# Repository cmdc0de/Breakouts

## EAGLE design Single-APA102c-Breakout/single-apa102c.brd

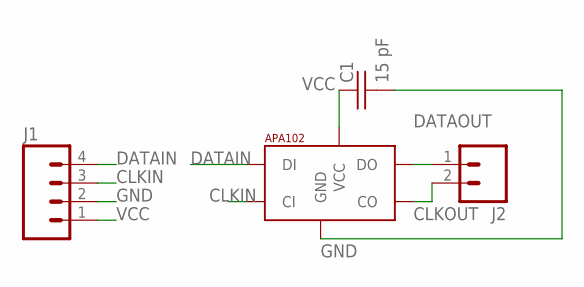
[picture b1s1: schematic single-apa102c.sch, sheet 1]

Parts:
C1: 15 pF; C0805K
J1: M04PTH; 1X04
J2: M02PTH; 1X02
U$1: APA1025050; APA102_5050

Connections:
CLKIN: J1.3, U$1.5 (CI)
CLKOUT: J2.2, U$1.2 (CO)
DATAIN: J1.4, U$1.4 (DI)
DATAOUT: J2.1, U$1.3 (DO)
GND: C1.2, J1.2, U$1.6 (GND)
VCC: C1.1, J1.1, U$1.1 (VCC)

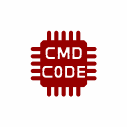
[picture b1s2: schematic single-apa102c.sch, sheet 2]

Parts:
U$2: CMD_C0DE_LOGOCMD_CODE_LOGO_TOP_COPPER; CMD_C0DE_LOGO_TOP_COPPER

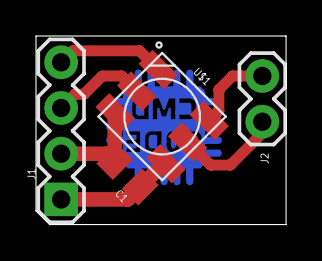
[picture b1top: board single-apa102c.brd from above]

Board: 2 copper layers, 13.9 x 10.5 mm, 5 parts (1 on the bottom side), 6 nets.

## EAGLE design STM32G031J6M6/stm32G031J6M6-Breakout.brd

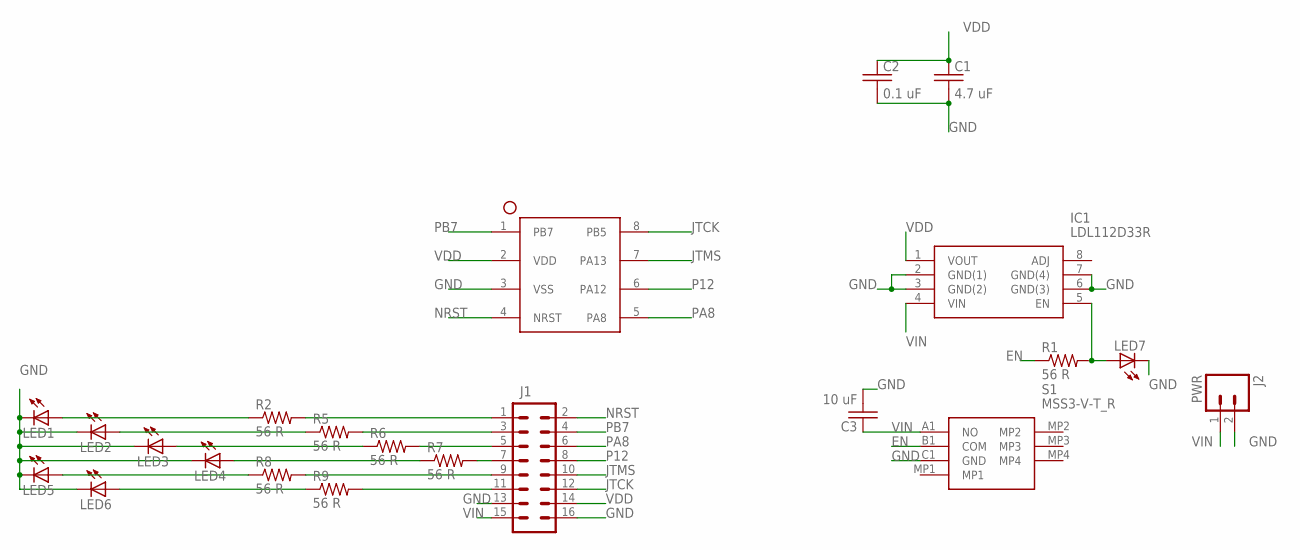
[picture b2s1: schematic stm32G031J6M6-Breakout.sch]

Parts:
C1: 4.7 uF; C0805K
C2: 0.1 uF; C0805K
C3: 10 uF; C0805K
IC1: LDL112D33R; SOIC127P600X175-8N
J1: M08X2; 2X8
J2: PWR; 1X02
LED1, LED2, LED3, LED4, LED5, LED6, LED7: LED1206; LED-1206
R1, R2, R5, R6, R7, R8, R9: 56 R; 1206
S1: MSS3-V-T_R; MSS3VTR
U$1: STM32G031S08N; SOIC127P600X175-8N

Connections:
EN: R1.1, S1.B1 (COM)
GND: C1.2, C2.2, C3.2, IC1.2 (GND(1)), IC1.3 (GND(2)), IC1.6 (GND(3)), IC1.7 (GND(4)), J1.13, J1.16, J2.2, LED1.C, LED2.C, LED3.C, LED4.C, LED5.C, LED6.C, LED7.C, S1.C1 (GND), U$1.3 (VSS)
JTCK: J1.12, U$1.8 (PB5)
JTMS: J1.10, U$1.7 (PA13)
unnamed: J1.1, R2.2
unnamed: J1.3, R5.2
unnamed: J1.5, R6.2
unnamed: J1.7, R7.2
unnamed: J1.9, R8.2
unnamed: J1.11, R9.2
unnamed: LED1.A, R2.1
unnamed: LED2.A, R5.1
unnamed: LED3.A, R6.1
unnamed: LED4.A, R7.1
unnamed: LED5.A, R8.1
unnamed: LED6.A, R9.1
unnamed: IC1.5 (EN), LED7.A, R1.2
NRST: J1.2, U$1.4 (NRST)
P12: J1.8, U$1.6 (PA12)
PA8: J1.6, U$1.5 (PA8)
PB7: J1.4, U$1.1 (PB7)
VDD: C1.1, C2.1, IC1.1 (VOUT), J1.14, U$1.2 (VDD)
VIN: C3.1, IC1.4 (VIN), J1.15, J2.1, S1.A1 (NO)

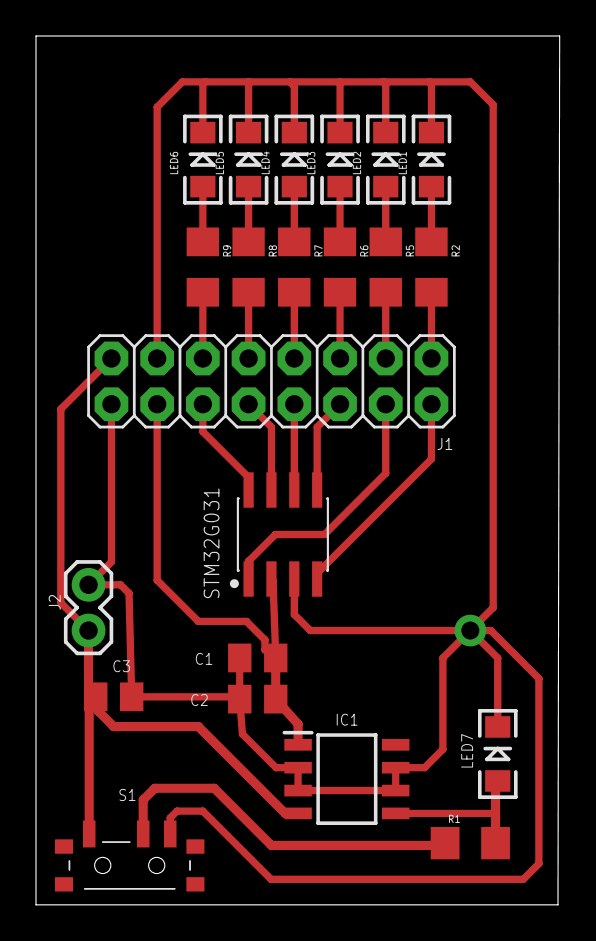
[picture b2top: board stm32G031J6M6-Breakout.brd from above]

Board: 2 copper layers, 29.1 x 48.3 mm, 22 parts (0 on the bottom side), 23 nets.

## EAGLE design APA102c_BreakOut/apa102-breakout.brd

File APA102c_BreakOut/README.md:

# APA102c_BreakOut
Holds eagle design and files for an apa102 50x50 breakout board

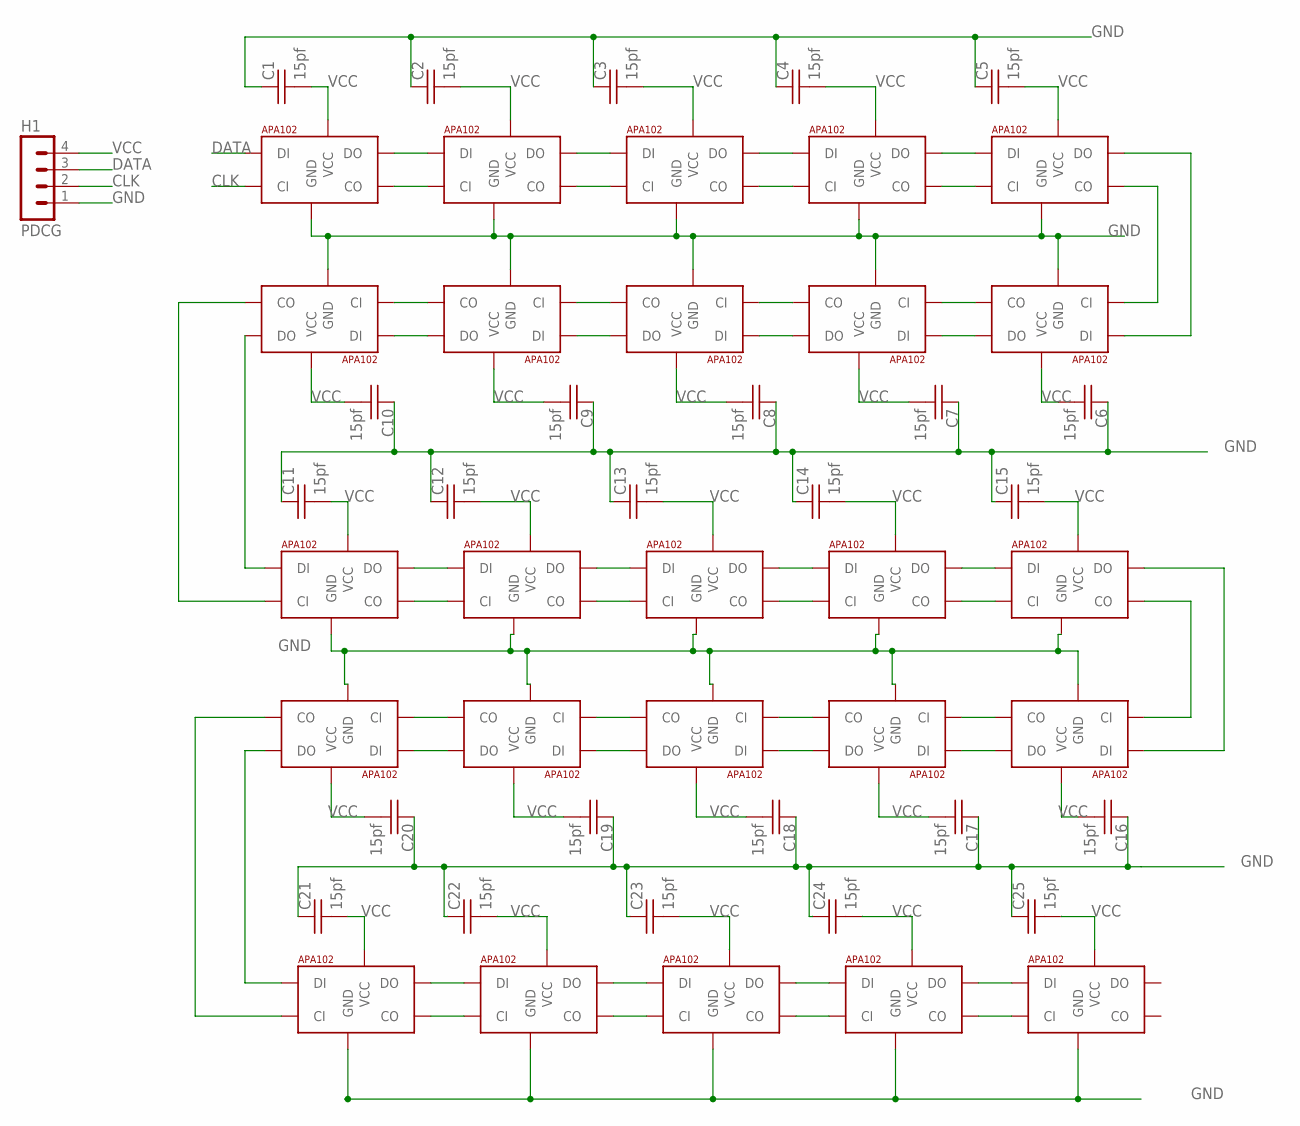
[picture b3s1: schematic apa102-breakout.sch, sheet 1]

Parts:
C1, C2, C3, C4, C5, C6, C7, C8, C9, C10, C11, C12, C13, C14, C15, C16, C17, C18, C19, C20, C21, C22, C23, C24, C25: 15pf; C0805
H1: PDCG; MA04-1
U$2, U$3, U$4, U$5, U$6, U$7, U$8, U$9, U$10, U$11, U$12, U$13, U$14, U$15, U$16, U$17, U$18, U$19, U$20, U$21, U$22, U$23, U$24, U$25, U$26: APA1025050; APA102_5050

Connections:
CLK: H1.2, U$2.5 (CI)
DATA: H1.3, U$2.4 (DI)
GND: C1.1, C2.1, C3.1, C4.1, C5.1, C6.1, C7.1, C8.1, C9.1, C10.1, C11.1, C12.1, C13.1, C14.1, C15.1, C16.1, C17.1, C18.1, C19.1, C20.1, C21.1, C22.1, C23.1, C24.1, C25.1, H1.1, U$2.6 (GND), U$3.6 (GND), U$4.6 (GND), U$5.6 (GND), U$6.6 (GND), U$7.6 (GND), U$8.6 (GND), U$9.6 (GND), U$10.6 (GND), U$11.6 (GND), U$12.6 (GND), U$13.6 (GND), U$14.6 (GND), U$15.6 (GND), U$16.6 (GND), U$17.6 (GND), U$18.6 (GND), U$19.6 (GND), U$20.6 (GND), U$21.6 (GND), U$22.6 (GND), U$23.6 (GND), U$24.6 (GND), U$25.6 (GND), U$26.6 (GND)
unnamed: U$2.3 (DO), U$3.4 (DI)
unnamed: U$2.2 (CO), U$3.5 (CI)
unnamed: U$3.3 (DO), U$4.4 (DI)
unnamed: U$3.2 (CO), U$4.5 (CI)
unnamed: U$4.3 (DO), U$5.4 (DI)
unnamed: U$4.2 (CO), U$5.5 (CI)
unnamed: U$5.3 (DO), U$6.4 (DI)
unnamed: U$5.2 (CO), U$6.5 (CI)
unnamed: U$6.3 (DO), U$7.4 (DI)
unnamed: U$6.2 (CO), U$7.5 (CI)
unnamed: U$7.3 (DO), U$8.4 (DI)
unnamed: U$7.2 (CO), U$8.5 (CI)
unnamed: U$8.2 (CO), U$9.5 (CI)
unnamed: U$8.3 (DO), U$9.4 (DI)
unnamed: U$9.2 (CO), U$10.5 (CI)
unnamed: U$9.3 (DO), U$10.4 (DI)
unnamed: U$10.2 (CO), U$11.5 (CI)
unnamed: U$10.3 (DO), U$11.4 (DI)
unnamed: U$11.2 (CO), U$12.5 (CI)
unnamed: U$11.3 (DO), U$12.4 (DI)
unnamed: U$12.3 (DO), U$13.4 (DI)
unnamed: U$12.2 (CO), U$13.5 (CI)
unnamed: U$13.3 (DO), U$14.4 (DI)
unnamed: U$13.2 (CO), U$14.5 (CI)
unnamed: U$14.3 (DO), U$15.4 (DI)
unnamed: U$14.2 (CO), U$15.5 (CI)
unnamed: U$15.3 (DO), U$16.4 (DI)
unnamed: U$15.2 (CO), U$16.5 (CI)
unnamed: U$16.3 (DO), U$17.4 (DI)
unnamed: U$16.2 (CO), U$17.5 (CI)
unnamed: U$17.3 (DO), U$18.4 (DI)
unnamed: U$17.2 (CO), U$18.5 (CI)
unnamed: U$18.2 (CO), U$19.5 (CI)
unnamed: U$18.3 (DO), U$19.4 (DI)
unnamed: U$19.2 (CO), U$20.5 (CI)
unnamed: U$19.3 (DO), U$20.4 (DI)
unnamed: U$20.2 (CO), U$21.5 (CI)
unnamed: U$20.3 (DO), U$21.4 (DI)
unnamed: U$21.3 (DO), U$22.4 (DI)
unnamed: U$21.2 (CO), U$22.5 (CI)
unnamed: U$22.3 (DO), U$23.4 (DI)
unnamed: U$22.2 (CO), U$23.5 (CI)
unnamed: U$23.3 (DO), U$24.4 (DI)
unnamed: U$23.2 (CO), U$24.5 (CI)
unnamed: U$24.3 (DO), U$25.4 (DI)
unnamed: U$24.2 (CO), U$25.5 (CI)
unnamed: U$25.3 (DO), U$26.4 (DI)
unnamed: U$25.2 (CO), U$26.5 (CI)
VCC: C1.2, C2.2, C3.2, C4.2, C5.2, C6.2, C7.2, C8.2, C9.2, C10.2, C11.2, C12.2, C13.2, C14.2, C15.2, C16.2, C17.2, C18.2, C19.2, C20.2, C21.2, C22.2, C23.2, C24.2, C25.2, H1.4, U$2.1 (VCC), U$3.1 (VCC), U$4.1 (VCC), U$5.1 (VCC), U$6.1 (VCC), U$7.1 (VCC), U$8.1 (VCC), U$9.1 (VCC), U$10.1 (VCC), U$11.1 (VCC), U$12.1 (VCC), U$13.1 (VCC), U$14.1 (VCC), U$15.1 (VCC), U$16.1 (VCC), U$17.1 (VCC), U$18.1 (VCC), U$19.1 (VCC), U$20.1 (VCC), U$21.1 (VCC), U$22.1 (VCC), U$23.1 (VCC), U$24.1 (VCC), U$25.1 (VCC), U$26.1 (VCC)

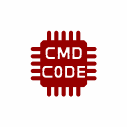
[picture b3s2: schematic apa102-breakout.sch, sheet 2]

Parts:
U$1: CMD_C0DE_LOGOCMD_C0DE_LOGO_TOP; CMD_C0DE_LOGO_TOP

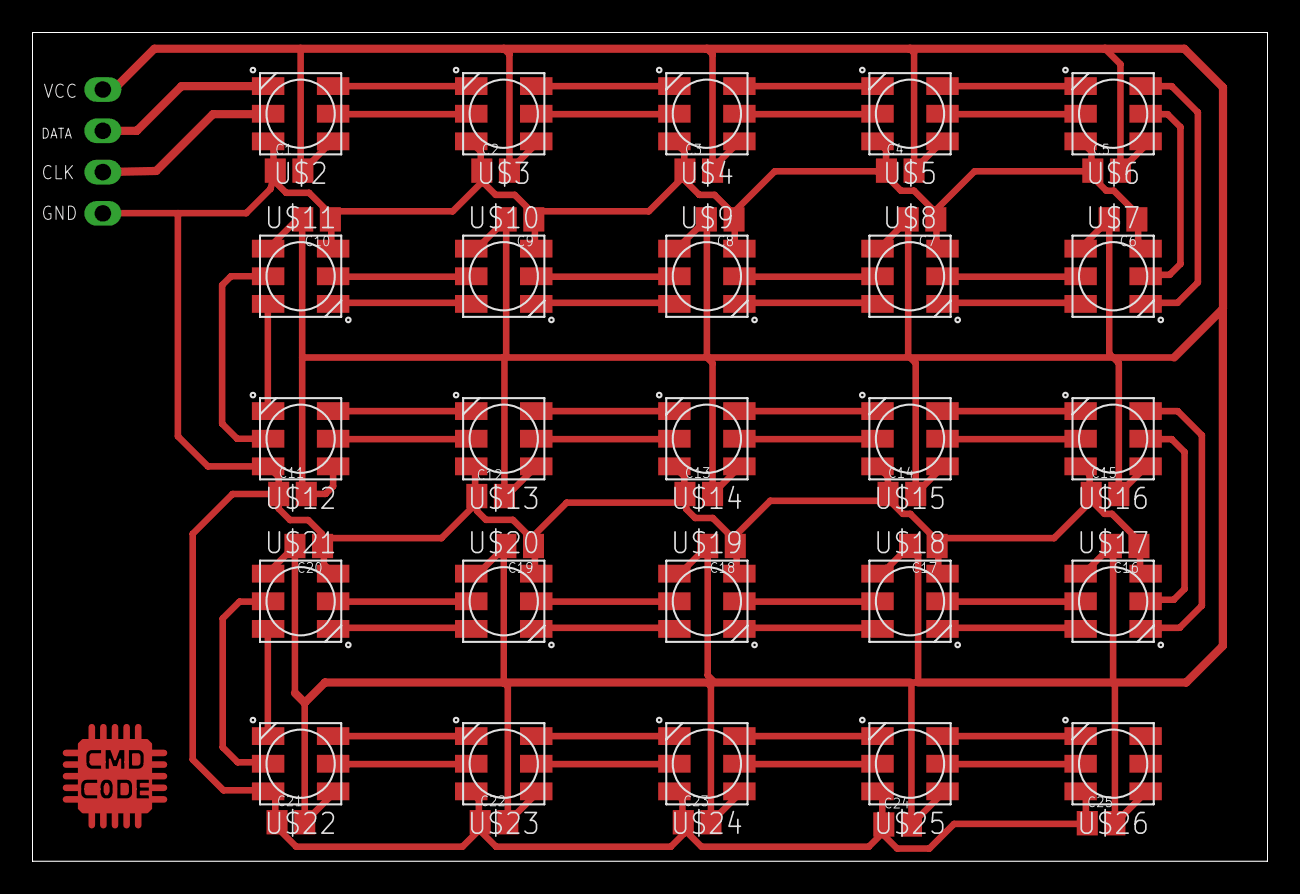
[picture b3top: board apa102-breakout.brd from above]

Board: 2 copper layers, 76.0 x 51.0 mm, 52 parts (1 on the bottom side), 52 nets.

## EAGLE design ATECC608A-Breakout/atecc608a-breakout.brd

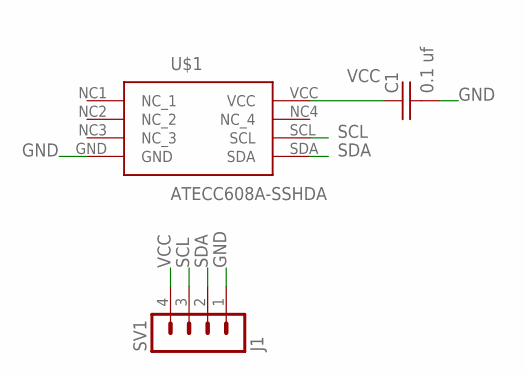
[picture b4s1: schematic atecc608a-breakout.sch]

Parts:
C1: 0.1 uf; C0805
SV1: J1; MA04-1
U$1: ATECC608A-SSHDA; 8-SOIC

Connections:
GND: C1.2, SV1.1, U$1.GND
SCL: SV1.3, U$1.SCL
SDA: SV1.2, U$1.SDA
VCC: C1.1, SV1.4, U$1.VCC

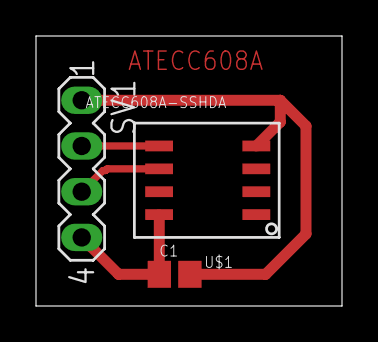
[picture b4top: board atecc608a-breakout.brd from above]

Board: 2 copper layers, 17.0 x 15.0 mm, 3 parts (0 on the bottom side), 4 nets.

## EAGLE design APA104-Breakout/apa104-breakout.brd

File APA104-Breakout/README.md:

# APA104-Breakout
Hardware files for a APA104 breakout board and number of mcu breakout boards and code to drive the apa 104

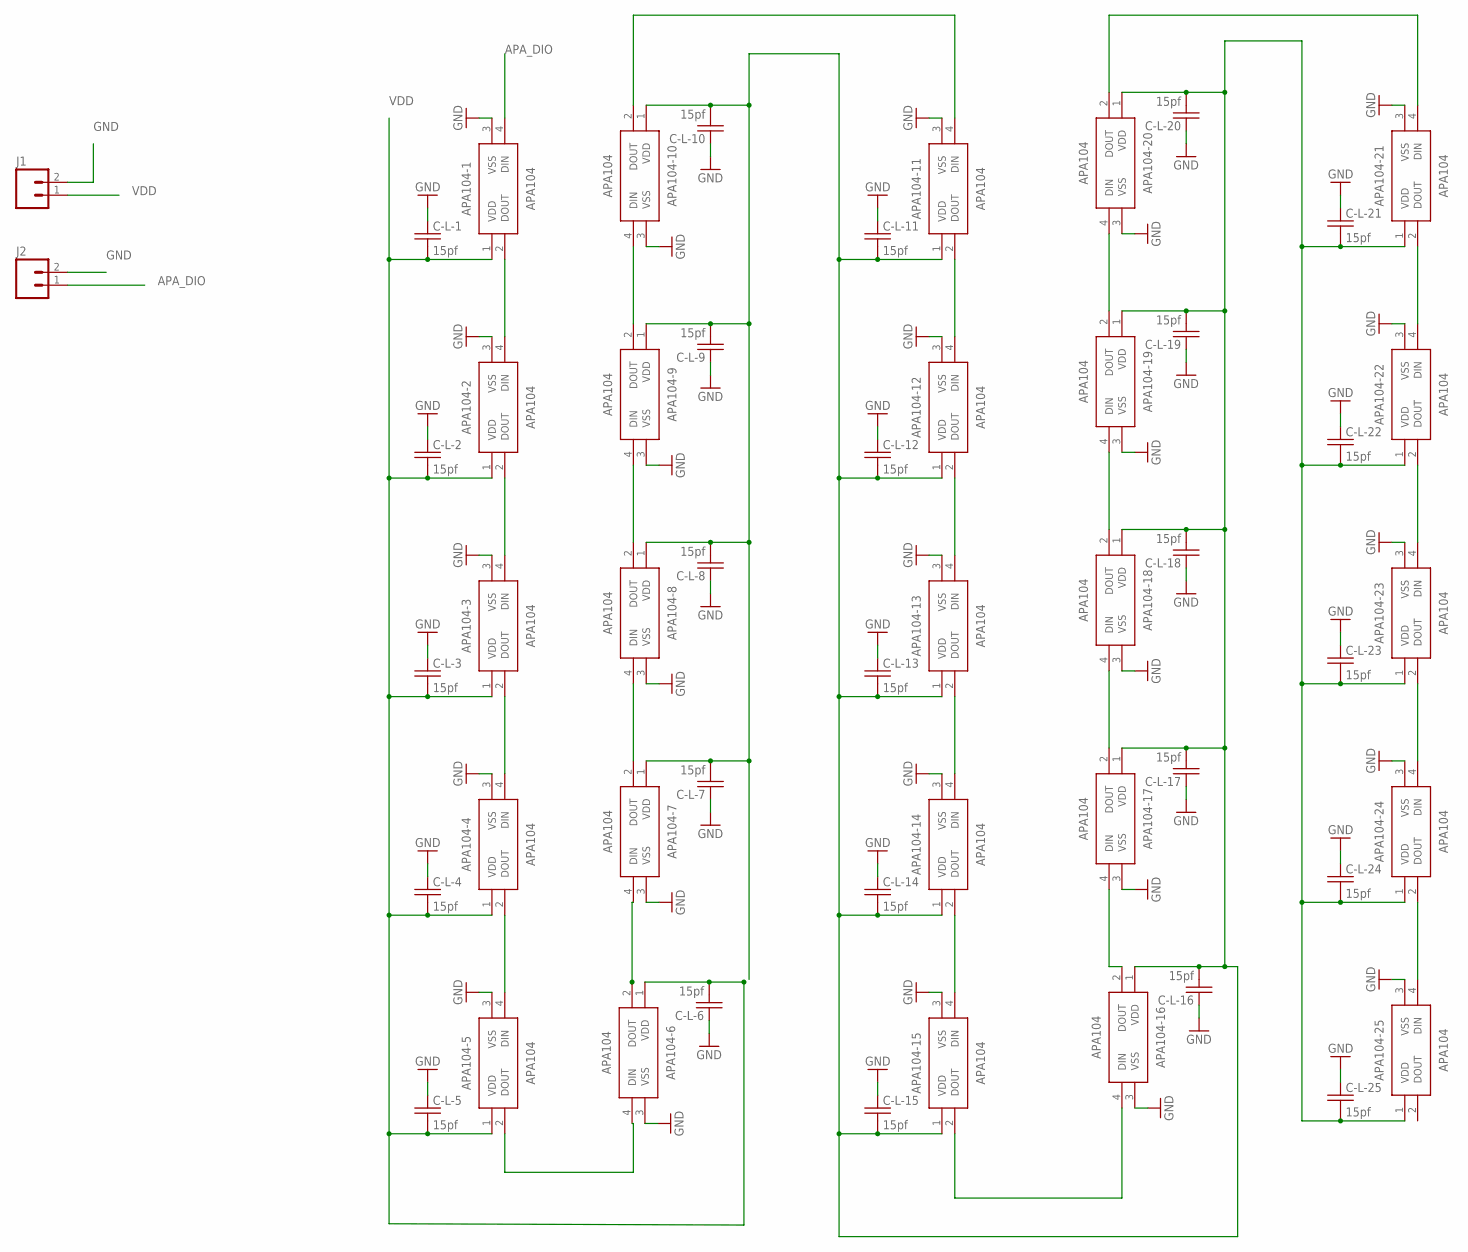
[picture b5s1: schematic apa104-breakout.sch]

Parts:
APA104-1, APA104-2, APA104-3, APA104-4, APA104-5, APA104-6, APA104-7, APA104-8, APA104-9, APA104-10, APA104-11, APA104-12, APA104-13, APA104-14, APA104-15, APA104-16, APA104-17, APA104-18, APA104-19, APA104-20, APA104-21, APA104-22, APA104-23, APA104-24, APA104-25: APA104
C-L-1, C-L-2, C-L-3, C-L-4, C-L-5, C-L-6, C-L-7, C-L-8, C-L-9, C-L-10, C-L-11, C-L-12, C-L-13, C-L-14, C-L-15, C-L-16, C-L-17, C-L-18, C-L-19, C-L-20, C-L-21, C-L-22, C-L-23, C-L-24, C-L-25: 15pf; C0805-VOLTA
J1, J2: M02PTH; 1X02

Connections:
APA_DIO: APA104-1.4 (DIN), J2.1
GND: APA104-1.3 (VSS), APA104-2.3 (VSS), APA104-3.3 (VSS), APA104-4.3 (VSS), APA104-5.3 (VSS), APA104-6.3 (VSS), APA104-7.3 (VSS), APA104-8.3 (VSS), APA104-9.3 (VSS), APA104-10.3 (VSS), APA104-11.3 (VSS), APA104-12.3 (VSS), APA104-13.3 (VSS), APA104-14.3 (VSS), APA104-15.3 (VSS), APA104-16.3 (VSS), APA104-17.3 (VSS), APA104-18.3 (VSS), APA104-19.3 (VSS), APA104-20.3 (VSS), APA104-21.3 (VSS), APA104-22.3 (VSS), APA104-23.3 (VSS), APA104-24.3 (VSS), APA104-25.3 (VSS), C-L-1.1, C-L-2.1, C-L-3.1, C-L-4.1, C-L-5.1, C-L-6.1, C-L-7.1, C-L-8.1, C-L-9.1, C-L-10.1, C-L-11.1, C-L-12.1, C-L-13.1, C-L-14.1, C-L-15.1, C-L-16.1, C-L-17.1, C-L-18.1, C-L-19.1, C-L-20.1, C-L-21.1, C-L-22.1, C-L-23.1, C-L-24.1, C-L-25.1, J1.2, J2.2
unnamed: APA104-2.2 (DOUT), APA104-3.4 (DIN)
unnamed: APA104-3.2 (DOUT), APA104-4.4 (DIN)
unnamed: APA104-4.2 (DOUT), APA104-5.4 (DIN)
unnamed: APA104-6.2 (DOUT), APA104-7.4 (DIN)
unnamed: APA104-5.2 (DOUT), APA104-6.4 (DIN)
unnamed: APA104-7.2 (DOUT), APA104-8.4 (DIN)
unnamed: APA104-8.2 (DOUT), APA104-9.4 (DIN)
unnamed: APA104-9.2 (DOUT), APA104-10.4 (DIN)
unnamed: APA104-10.2 (DOUT), APA104-11.4 (DIN)
unnamed: APA104-11.2 (DOUT), APA104-12.4 (DIN)
unnamed: APA104-12.2 (DOUT), APA104-13.4 (DIN)
unnamed: APA104-13.2 (DOUT), APA104-14.4 (DIN)
unnamed: APA104-14.2 (DOUT), APA104-15.4 (DIN)
unnamed: APA104-15.2 (DOUT), APA104-16.4 (DIN)
unnamed: APA104-16.2 (DOUT), APA104-17.4 (DIN)
unnamed: APA104-17.2 (DOUT), APA104-18.4 (DIN)
unnamed: APA104-18.2 (DOUT), APA104-19.4 (DIN)
unnamed: APA104-19.2 (DOUT), APA104-20.4 (DIN)
unnamed: APA104-20.2 (DOUT), APA104-21.4 (DIN)
unnamed: APA104-21.2 (DOUT), APA104-22.4 (DIN)
unnamed: APA104-22.2 (DOUT), APA104-23.4 (DIN)
unnamed: APA104-23.2 (DOUT), APA104-24.4 (DIN)
unnamed: APA104-24.2 (DOUT), APA104-25.4 (DIN)
unnamed: APA104-1.2 (DOUT), APA104-2.4 (DIN)
VDD: APA104-1.1 (VDD), APA104-2.1 (VDD), APA104-3.1 (VDD), APA104-4.1 (VDD), APA104-5.1 (VDD), APA104-6.1 (VDD), APA104-7.1 (VDD), APA104-8.1 (VDD), APA104-9.1 (VDD), APA104-10.1 (VDD), APA104-11.1 (VDD), APA104-12.1 (VDD), APA104-13.1 (VDD), APA104-14.1 (VDD), APA104-15.1 (VDD), APA104-16.1 (VDD), APA104-17.1 (VDD), APA104-18.1 (VDD), APA104-19.1 (VDD), APA104-20.1 (VDD), APA104-21.1 (VDD), APA104-22.1 (VDD), APA104-23.1 (VDD), APA104-24.1 (VDD), APA104-25.1 (VDD), C-L-1.2, C-L-2.2, C-L-3.2, C-L-4.2, C-L-5.2, C-L-6.2, C-L-7.2, C-L-8.2, C-L-9.2, C-L-10.2, C-L-11.2, C-L-12.2, C-L-13.2, C-L-14.2, C-L-15.2, C-L-16.2, C-L-17.2, C-L-18.2, C-L-19.2, C-L-20.2, C-L-21.2, C-L-22.2, C-L-23.2, C-L-24.2, C-L-25.2, J1.1

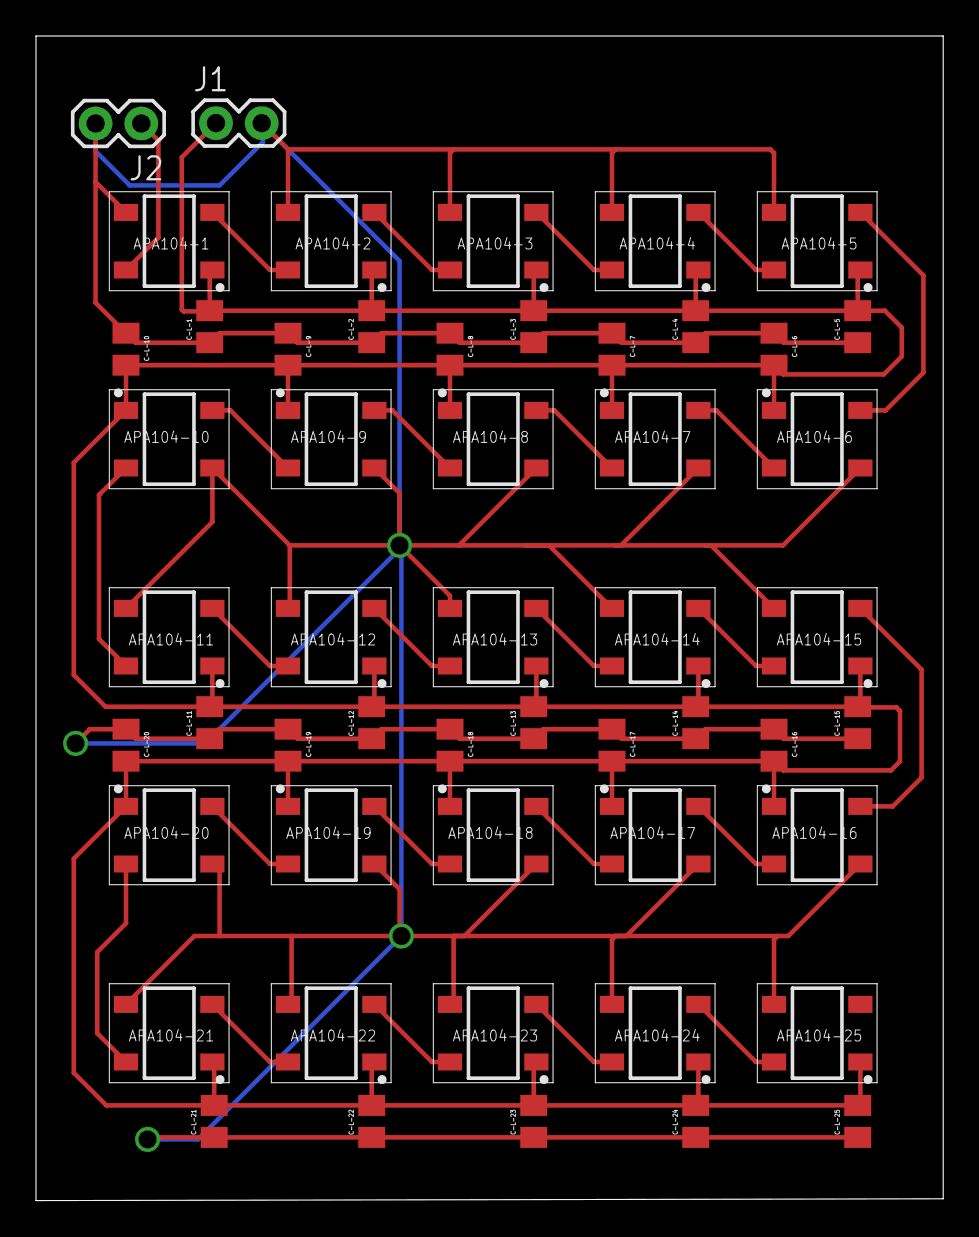
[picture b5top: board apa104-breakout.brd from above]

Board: 2 copper layers, 50.4 x 64.7 mm, 52 parts (0 on the bottom side), 27 nets.

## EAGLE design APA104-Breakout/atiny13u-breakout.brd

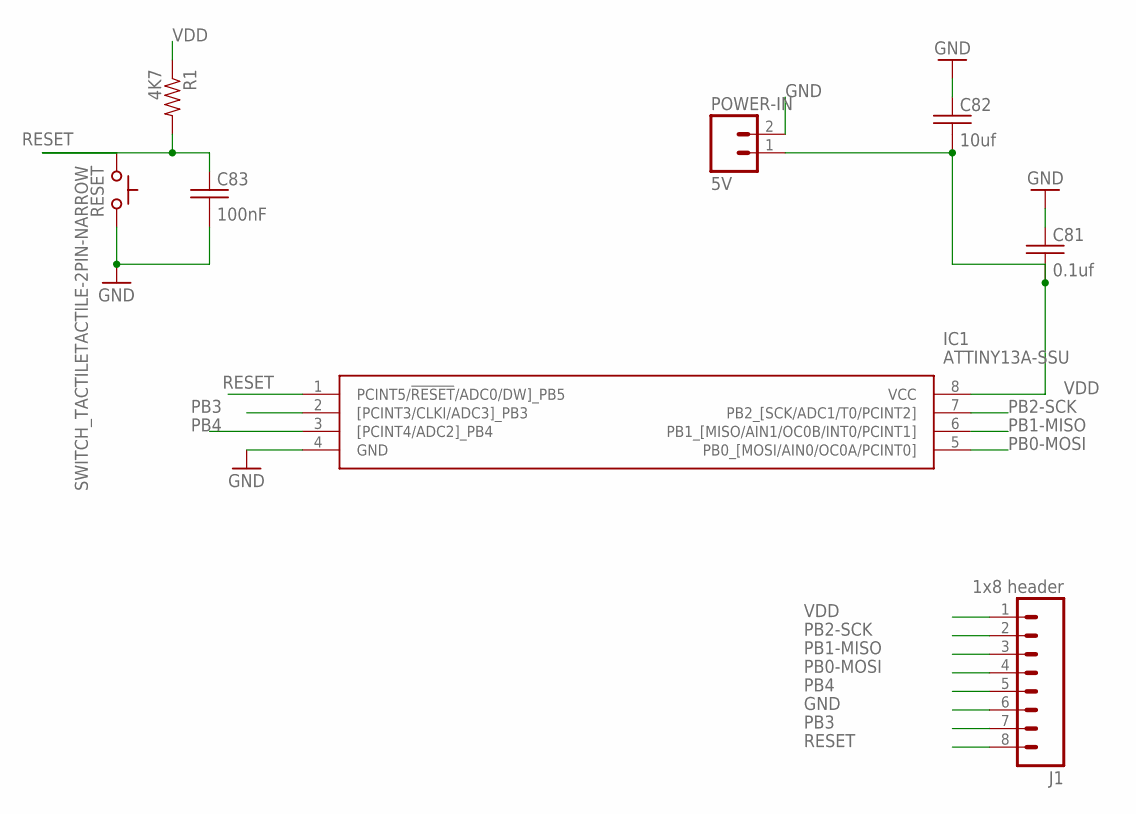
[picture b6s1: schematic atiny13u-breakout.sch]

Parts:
C81: 0.1uf; C0805-VOLTA
C82: 10uf; C0805-VOLTA
C83: 100nF; C0805-VOLTA
IC1: ATTINY13A-SSU; SOIC127P600X175-8N
J1: 1x8 header; 1X08
POWER-IN: 5V; 1X02
R1: 4K7; 0805
RESET: SWITCH_TACTILETACTILE-2PIN-NARROW; TACTILE-2PIN-NARROW

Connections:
GND: C81.1, C82.1, C83.2, IC1.4 (GND), J1.6, POWER-IN.2, RESET.P$1 (A)
PB0-MOSI: IC1.5 (PB0_[MOSI/AIN0/OC0A/PCINT0]), J1.4
PB1-MISO: IC1.6 (PB1_[MISO/AIN1/OC0B/INT0/PCINT1]), J1.3
PB2-SCK: IC1.7 (PB2_[SCK/ADC1/T0/PCINT2]), J1.2
PB3: IC1.2 ([PCINT3/CLKI/ADC3]_PB3), J1.7
PB4: IC1.3 ([PCINT4/ADC2]_PB4), J1.5
RESET: C83.1, IC1.1 (PCINT5/!RESET!/ADC0/DW]_PB5), J1.8, R1.2, RESET.P$2 (C)
VDD: C81.2, C82.2, IC1.8 (VCC), J1.1, POWER-IN.1, R1.1

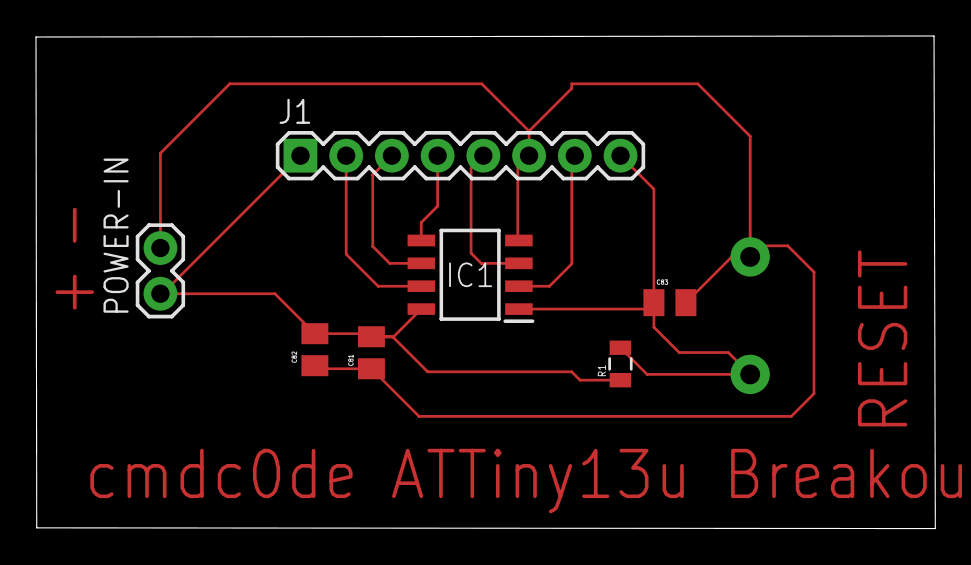
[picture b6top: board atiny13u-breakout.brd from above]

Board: 2 copper layers, 50.0 x 27.4 mm, 8 parts (1 on the bottom side), 8 nets.

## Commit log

2018-11-23 adding all breakout boards to 1 repo
2018-11-23 updated routing again
2018-11-23 docs
2018-11-23 adding gerbers
2019-10-27 added silk screen
2019-12-31 adding breakout board for stm32g031
2019-12-31 switched packages for caps so I could only work with 1/64 inch bits
2020-01-11 removed reset button as it was wrong AND don't need it
2020-01-13 test firmware
2020-05-02 adding rgb breakout
2020-06-06 new breakout
2020-10-24 infinity mirror single apa102c
2020-10-24 tweaking size to fit in infinity mirror
2020-10-25 angled apa102c to help with 3d printing
2020-10-30 moved led to a 45 degree angle
2020-11-16 adding outputs to right side
